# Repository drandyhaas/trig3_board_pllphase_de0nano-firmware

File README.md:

# trig3_board_pllphase_de0nano-firmware
Firmware for the Gershow FPGA worm analysis

Open coincidence.qpf with Quartus (tested with version 18.0.0)

## Serial command set
- 0: send the firmware version				
- 1 + byte: set deadticks
- 2 + byte: set firingticks
- 3: toggle output enable
- 4: toggle clk inputs
- 5 + byte: set clock phase (phase shift = byte/128 * 360)
- 6 + byte: set output1 phase mask		
- 7 + byte: set output2 phase mask
- 8: toggle PMT passthrough
- 9: toggle phase step direction
- 10: send histogram (4 bins for now) 
- 11: toggle vetopmtlast
- 12: adjust clock phase (c1)

## outputs
- A6: out1 : coax_out[2] 
- B6: out2 : coax_out[3] 
- N11: test pulse : coax_out[0]
- P9: 4x clock for test pulse : coax_out[1]
- F9: phase shifted? input clock : coax_out[4] 
- E7: lvds clock (4x) phase shifted : coax_out[5]
- C11: echos differential clock input
- E11: echos single ended clock input
- J13 - active clock
- P11 - clock bad 0
- D8 - clock bad 1

## inputs
- R9/T9 - differential clock input (note that board has resistor networks to accept negative going ac coupled signal)
- A8 - singled ended clock input
- R16/P16 - differential pmt input (board has resistor network to accept AC coupled differential signal)
- L15 - single ended pmt input

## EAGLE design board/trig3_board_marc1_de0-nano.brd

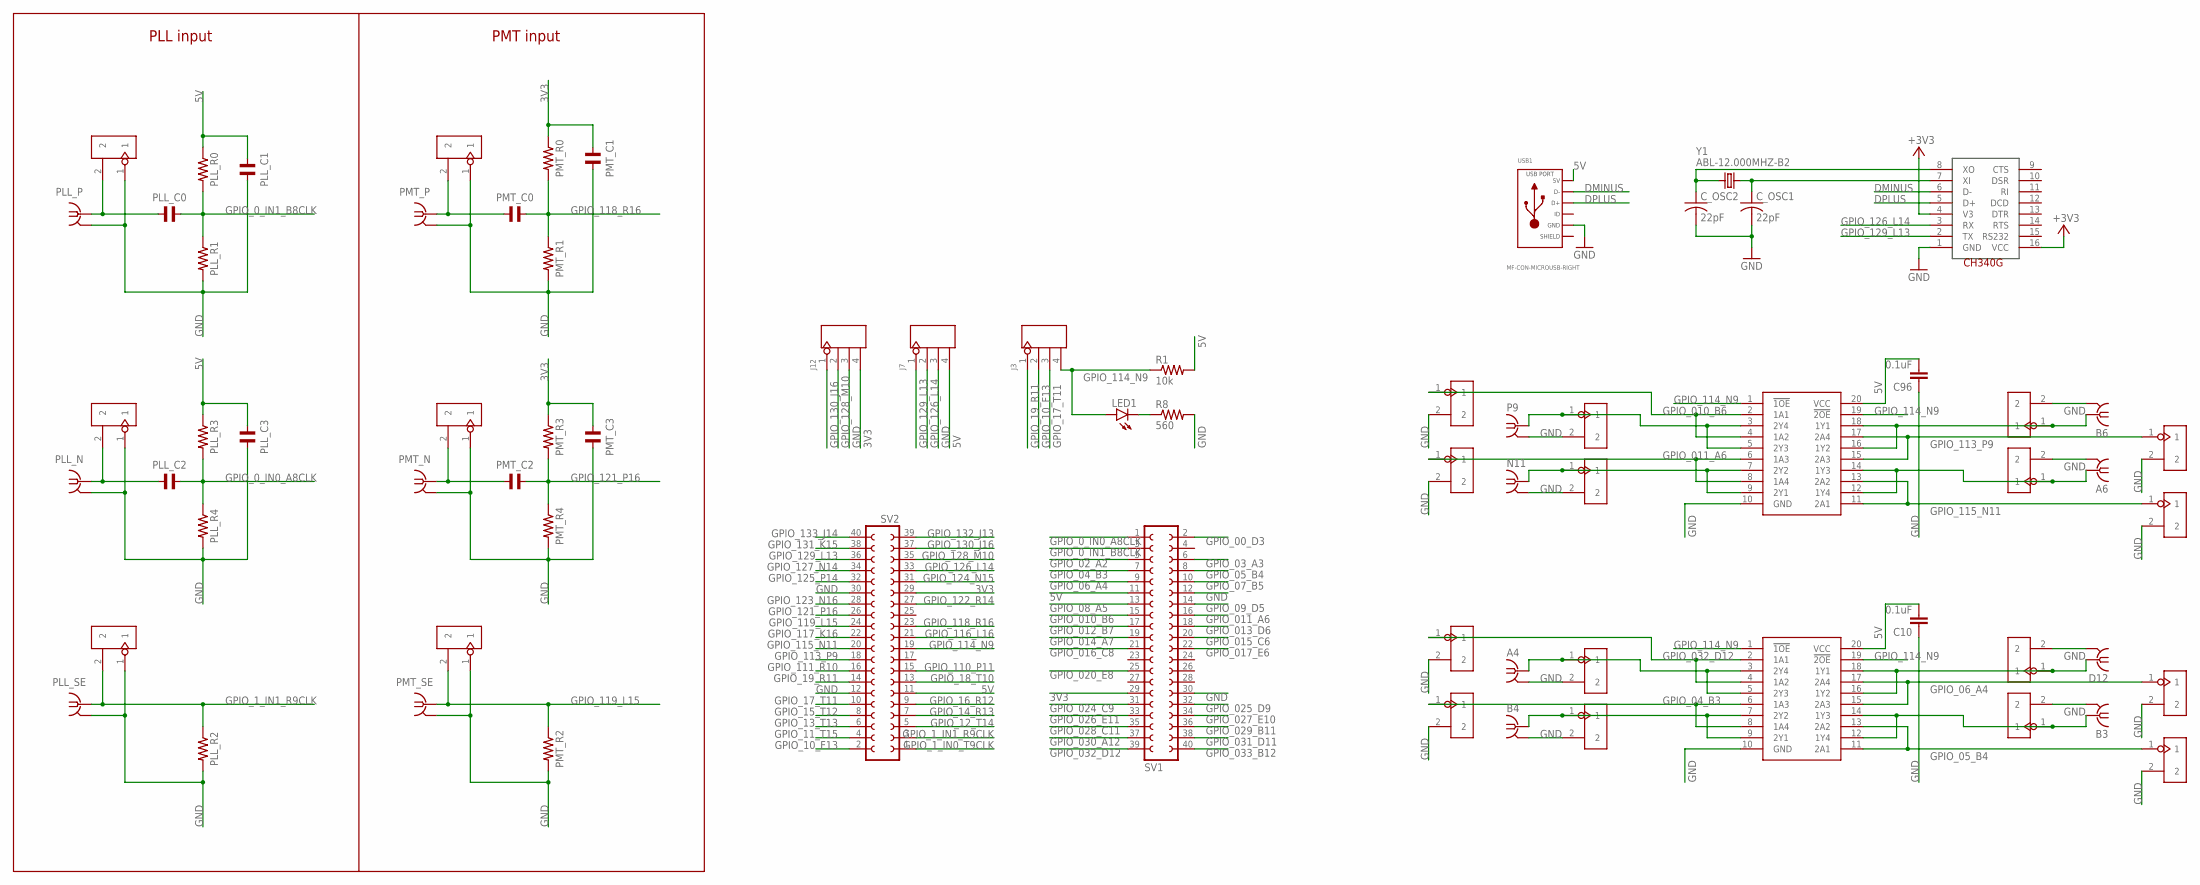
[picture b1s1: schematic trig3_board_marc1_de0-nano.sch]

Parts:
A4, A6: BU-SMB-V
B3, B4, B6: BU-SMB-V
C10, C96: 0.1uF; 0805
C_OSC1, C_OSC2: 22pF; C0603
D12: BU-SMB-V
J3, J7, J12: 4p-2.54; H4-2.54
LED1: red; CHIP-LED0805
N11: BU-SMB-V
OJ41, OJ42, OJ43, OJ44, OJ45, OJ46, OJ47, OJ48, OJ89, OJ90, OJ91, OJ92, OJ93, OJ94, OJ95, OJ96: 2p-2.54; H2-2.54
P9: BU-SMB-V
PLL_C0, PLL_C2: 1uF; C0805
PLL_C1: 0.1uF; C0805
PLL_C3: CAPACITOR_NP_0805; C0805
PLL_N: BU-SMB-V
PLL_N_J, PLL_N_J1: 2p-2.54; H2-2.54
PLL_P: BU-SMB-V
PLL_P_J: 2p-2.54; H2-2.54
PLL_R0, PLL_R1, PLL_R3, PLL_R4: RESISTOR_0805; R0805
PLL_R2: 50ohm; R0805
PLL_SE: BU-SMB-V
PMT_C0, PMT_C2: 1uF; C0805
PMT_C1: 0.1uF; C0805
PMT_C3: CAPACITOR_NP_0805; C0805
PMT_N: BU-SMB-V
PMT_N_J, PMT_N_J1: 2p-2.54; H2-2.54
PMT_P: BU-SMB-V
PMT_P_J: 2p-2.54; H2-2.54
PMT_R0, PMT_R1, PMT_R3, PMT_R4: RESISTOR_0805; R0805
PMT_R2: 50ohm; R0805
PMT_SE: BU-SMB-V
R1: 10k; R0805
R8: 560; R0805
SV1, SV2: FE20-2
U340G: CH340G; SOIC16
USB1: MF-CON-MICROUSB-RIGHT; 10118193-0001LF
VSLUE5, VSLUE11: SN74ACT244DW; SOIC127P1030X265-20N
Y1: ABL-12.000MHZ-B2; HC49US

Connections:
3V3: J12.4, PMT_C1.P$1, PMT_C3.P$1, PMT_R0.P$1, PMT_R3.P$1, SV1.29, SV2.29
5V: C10.2, C96.2, J7.4, PLL_C1.P$1, PLL_C3.P$1, PLL_R0.P$1, PLL_R3.P$1, R1.2, SV1.11, SV2.11, USB1.1 (5V), VSLUE5.20 (VCC), VSLUE11.20 (VCC)
+3V3: U340G.4 (V3), U340G.16 (VCC)
DMINUS: U340G.6 (D-), USB1.2 (D-)
DPLUS: U340G.5 (D+), USB1.3 (D+)
GND: A4.2, A4.3 (2), A4.4 (2), A4.5 (2), A6.2, A6.3 (2), A6.4 (2), A6.5 (2), B3.2, B3.3 (2), B3.4 (2), B3.5 (2), B4.2, B4.3 (2), B4.4 (2), B4.5 (2), B6.2, B6.3 (2), B6.4 (2), B6.5 (2), C10.1, C96.1, C_OSC1.2, C_OSC2.2, D12.2, D12.3 (2), D12.4 (2), D12.5 (2), J7.3, J12.3, N11.2, N11.3 (2), N11.4 (2), N11.5 (2), OJ41.2, OJ42.2, OJ43.2, OJ44.2, OJ45.2, OJ46.2, OJ47.2, OJ48.2, OJ89.2, OJ90.2, OJ91.2, OJ92.2, OJ93.2, OJ94.2, OJ95.2, OJ96.2, P9.2, P9.3 (2), P9.4 (2), P9.5 (2), PLL_C1.P$2, PLL_C3.P$2, PLL_N.2, PLL_N.3 (2), PLL_N.4 (2), PLL_N.5 (2), PLL_N_J.1, PLL_N_J1.1, PLL_P.2, PLL_P.3 (2), PLL_P.4 (2), PLL_P.5 (2), PLL_P_J.1, PLL_R1.P$2, PLL_R2.P$2, PLL_R4.P$2, PLL_SE.2, PLL_SE.3 (2), PLL_SE.4 (2), PLL_SE.5 (2), PMT_C1.P$2, PMT_C3.P$2, PMT_N.2, PMT_N.3 (2), PMT_N.4 (2), PMT_N.5 (2), PMT_N_J.1, PMT_N_J1.1, PMT_P.2, PMT_P.3 (2), PMT_P.4 (2), PMT_P.5 (2), PMT_P_J.1, PMT_R1.P$2, PMT_R2.P$2, PMT_R4.P$2, PMT_SE.2, PMT_SE.3 (2), PMT_SE.4 (2), PMT_SE.5 (2), R8.2, SV1.12, SV1.30, SV2.12, SV2.30, U340G.1 (GND), USB1.5 (GND), VSLUE5.10 (GND), VSLUE11.10 (GND)
GPIO_00_D3: SV1.2
GPIO_0_IN0_A8CLK: PLL_C2.P$2, PLL_R3.P$2, PLL_R4.P$1, SV1.1
GPIO_0_IN1_B8CLK: PLL_C0.P$2, PLL_R0.P$2, PLL_R1.P$1, SV1.3
GPIO_1_IN0_T9CLK: SV2.1
GPIO_1_IN1_R9CLK: PLL_N_J1.2, PLL_R2.P$1, PLL_SE.1, SV2.3
GPIO_02_A2: SV1.5
GPIO_03_A3: SV1.6
GPIO_04_B3: OJ96.1, SV1.7, VSLUE11.6 (1A3), VSLUE11.8 (1A4)
GPIO_05_B4: OJ94.1, SV1.8, VSLUE11.11 (2A1), VSLUE11.13 (2A2)
GPIO_06_A4: OJ93.1, SV1.9, VSLUE11.15 (2A3), VSLUE11.17 (2A4)
GPIO_07_B5: SV1.10
GPIO_08_A5: SV1.13
GPIO_09_D5: SV1.14
GPIO_010_B6: OJ47.1, SV1.15, VSLUE5.2 (1A1), VSLUE5.4 (1A2)
GPIO_10_F13: J3.2, SV2.2
GPIO_011_A6: OJ48.1, SV1.16, VSLUE5.6 (1A3), VSLUE5.8 (1A4)
GPIO_11_T15: SV2.4
GPIO_012_B7: SV1.17
GPIO_12_T14: SV2.5
GPIO_013_D6: SV1.18
GPIO_13_T13: SV2.6
GPIO_014_A7: SV1.19
GPIO_14_R13: SV2.7
GPIO_015_C6: SV1.20
GPIO_15_T12: SV2.8
GPIO_016_C8: SV1.21
GPIO_16_R12: SV2.9
GPIO_017_E6: SV1.22
GPIO_17_T11: J3.3, SV2.10
GPIO_18_T10: SV2.13
GPIO_19_R11: J3.1, SV2.14
GPIO_020_E8: SV1.25
GPIO_024_C9: SV1.31
GPIO_025_D9: SV1.32
GPIO_026_E11: SV1.33
GPIO_027_E10: SV1.34
GPIO_028_C11: SV1.35
GPIO_029_B11: SV1.36
GPIO_030_A12: SV1.37
GPIO_031_D11: SV1.38
GPIO_032_D12: OJ95.1, SV1.39, VSLUE11.2 (1A1), VSLUE11.4 (1A2)
GPIO_033_B12: SV1.40
GPIO_110_P11: SV2.15
GPIO_111_R10: SV2.16
GPIO_113_P9: OJ45.1, SV2.18, VSLUE5.15 (2A3), VSLUE5.17 (2A4)
GPIO_114_N9: J3.4, LED1.A, R1.1, SV2.19, VSLUE5.1 (!1OE), VSLUE5.19 (!2OE), VSLUE11.1 (!1OE), VSLUE11.19 (!2OE)
GPIO_115_N11: OJ46.1, SV2.20, VSLUE5.11 (2A1), VSLUE5.13 (2A2)
GPIO_116_L16: SV2.21
GPIO_117_K16: SV2.22
GPIO_118_R16: PMT_C0.P$2, PMT_R0.P$2, PMT_R1.P$1, SV2.23
GPIO_119_L15: PMT_N_J1.2, PMT_R2.P$1, PMT_SE.1, SV2.24
GPIO_121_P16: PMT_C2.P$2, PMT_R3.P$2, PMT_R4.P$1, SV2.26
GPIO_122_R14: SV2.27
GPIO_123_N16: SV2.28
GPIO_124_N15: SV2.31
GPIO_125_P14: SV2.32
GPIO_126_L14: J7.2, SV2.33, U340G.3 (RX)
GPIO_127_N14: SV2.34
GPIO_128_M10: J12.2, SV2.35
GPIO_129_L13: J7.1, SV2.36, U340G.2 (TX)
GPIO_130_J16: J12.1, SV2.37
GPIO_131_K15: SV2.38
GPIO_132_J13: SV2.39
GPIO_133_J14: SV2.40
unnamed: PMT_C0.P$1, PMT_P.1, PMT_P_J.2
unnamed: PMT_C2.P$1, PMT_N.1, PMT_N_J.2
unnamed: LED1.C, R8.1
unnamed: PLL_C0.P$1, PLL_P.1, PLL_P_J.2
unnamed: PLL_C2.P$1, PLL_N.1, PLL_N_J.2
unnamed: C_OSC1.1, U340G.7 (XI), Y1.1
unnamed: C_OSC2.1, U340G.8 (XO), Y1.2
OUT21: B6.1, OJ44.1, VSLUE5.16 (1Y2), VSLUE5.18 (1Y1)
OUT22: A6.1, OJ43.1, VSLUE5.12 (1Y4), VSLUE5.14 (1Y3)
OUT23: OJ41.1, P9.1, VSLUE5.3 (2Y4), VSLUE5.5 (2Y3)
OUT24: N11.1, OJ42.1, VSLUE5.7 (2Y2), VSLUE5.9 (2Y1)
OUT45: D12.1, OJ92.1, VSLUE11.16 (1Y2), VSLUE11.18 (1Y1)
OUT46: B3.1, OJ91.1, VSLUE11.12 (1Y4), VSLUE11.14 (1Y3)
OUT47: A4.1, OJ89.1, VSLUE11.3 (2Y4), VSLUE11.5 (2Y3)
OUT48: B4.1, OJ90.1, VSLUE11.7 (2Y2), VSLUE11.9 (2Y1)
SLD: USB1.S1 (SLD), USB1.S2 (SLD), USB1.S3 (SLD), USB1.S4 (SLD)

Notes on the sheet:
PLL input
PMT input

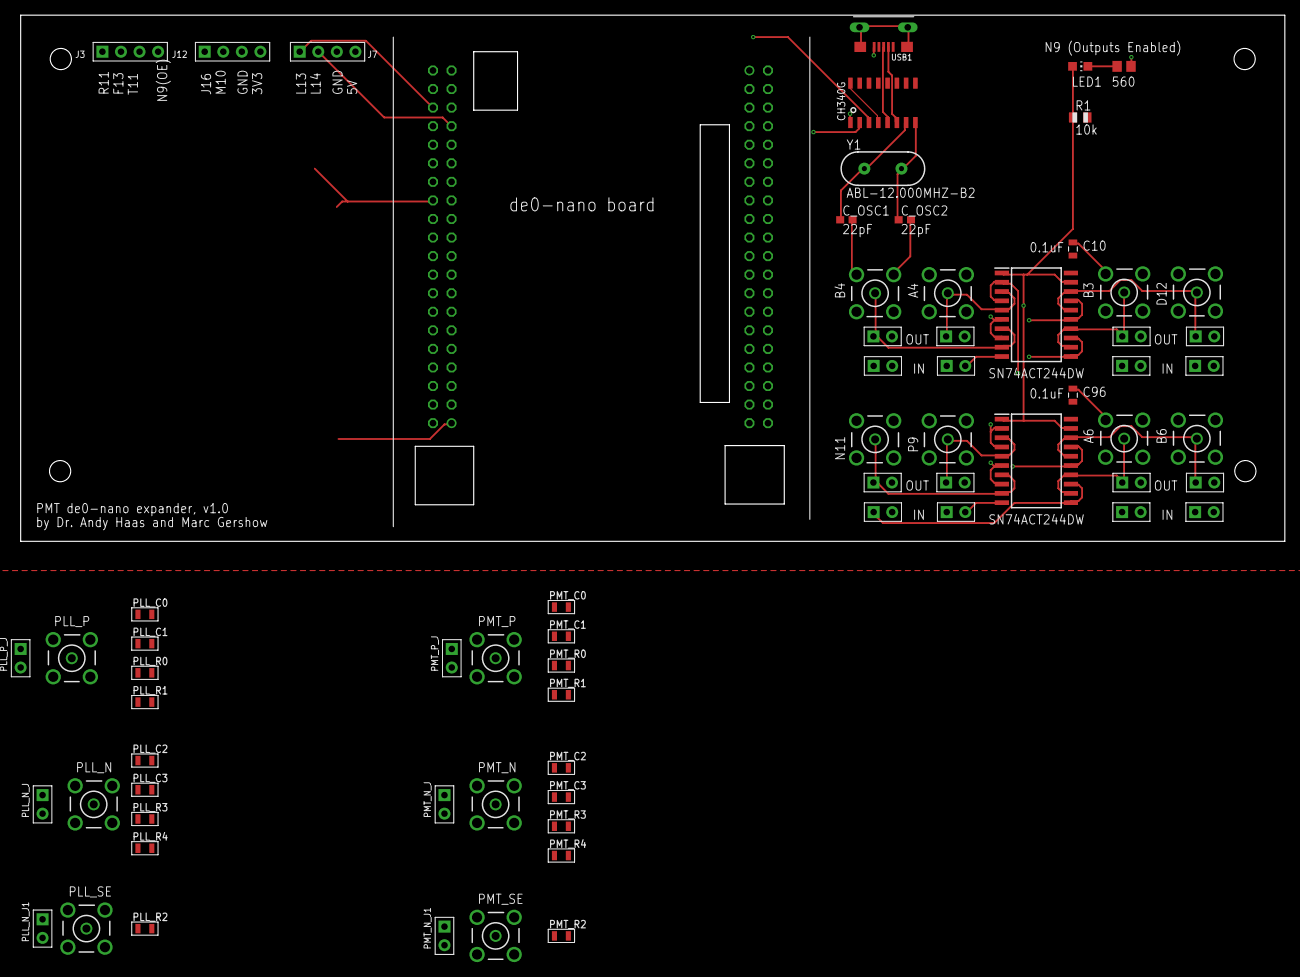
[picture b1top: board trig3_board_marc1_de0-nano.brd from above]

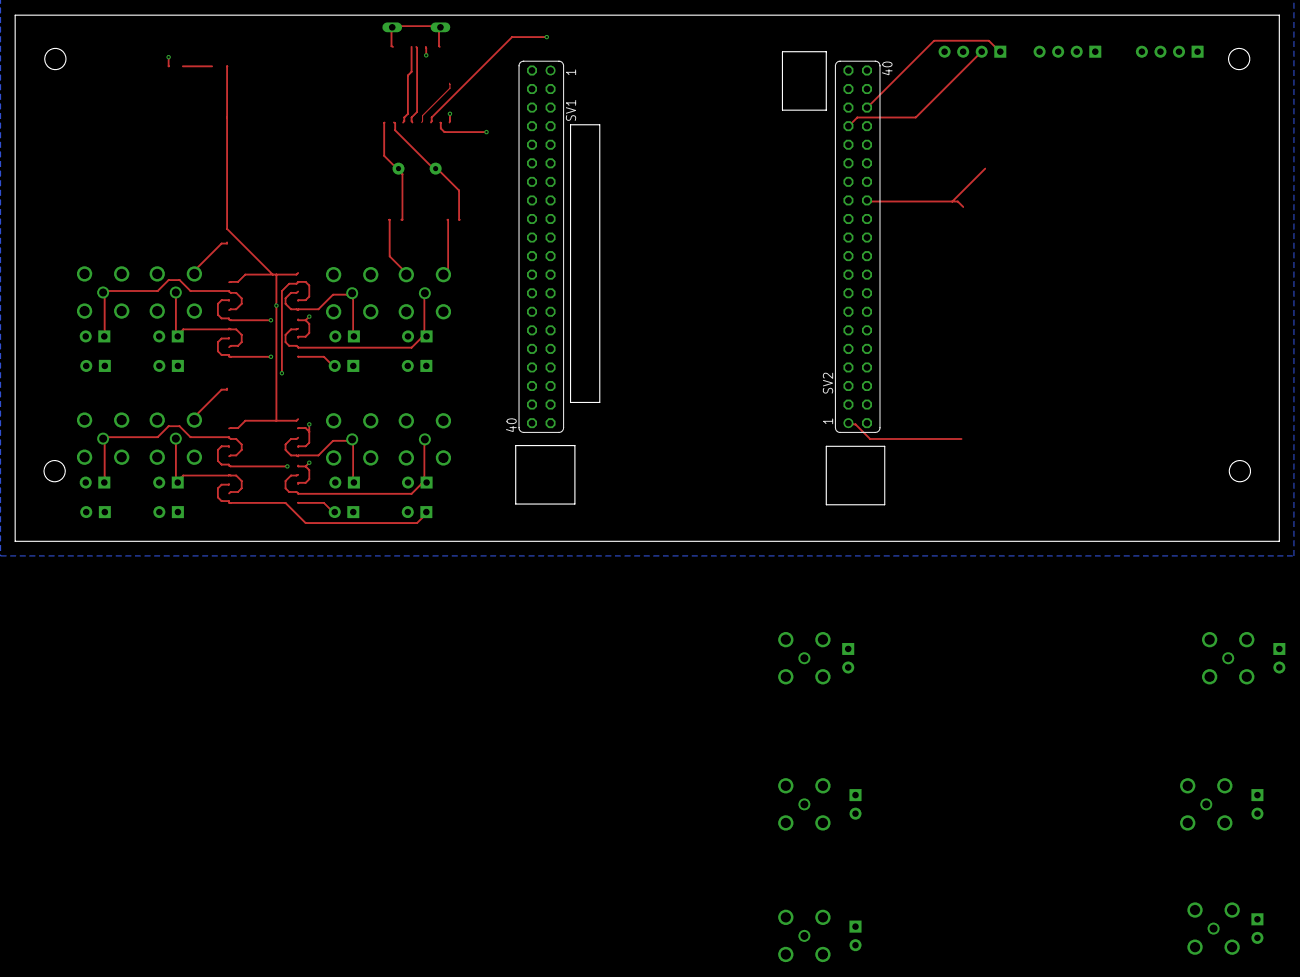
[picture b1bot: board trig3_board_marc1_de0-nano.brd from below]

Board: 4 copper layers, 173.0 x 72.0 mm, 71 parts (2 on the bottom side), 44 nets.

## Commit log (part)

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2020-01-23 initial checkin, working with 4 bins
2020-01-23 cleaner
2020-01-23 after compilation
2020-01-23 cleaner 2
2020-01-23 update for new location
2020-01-23 update to 8 bins
2020-02-19 changed 80Mhz clock input to LVDS
    required changes to logic family on some pins 3.3V -> 2.5V
    required override IO_MAXIMUM_TOGGLE_RATE to 0 MHz on enable outputs
2020-02-19 wrote programming file
2020-02-19 added single ended clock input at A8 with automatic selector
2020-02-20 changed pll bandwidth to low
    added debugging output signals to PLL
2020-02-25 added ability to reset PLL phase
    switched default clock to 70 MHz
2020-02-25 programs ok on lab computer
2020-02-25 board
2020-02-25 slim it down and add usb-serial
2020-02-25 for slimmed down board
2020-02-25 now set phase directly instead of incrementally
    to adjust phase: 5 byte; phase is set to byte by resetting PLL and then stepping byte times.
2020-02-25 set photon detection by mask
2020-02-26 histogram outputs 8 bins
2020-03-12 updated board schematics: input circuit redesign
2020-09-24 trying to generate ipi histogram; veto pulses too close together
2020-09-24 added serial command to set veto counter; updated firmware version
2020-09-24 get version works
2020-09-25 changed pin assignments
2020-09-29 updated to give debugging outputs
    cycle toggle on c16
    any photon on e7
2020-09-30 added debug - put clock input into lvds
2020-10-05 trimming down led_4.v and rewriting to use shift registers, eliminate for loops
2020-10-05 trying to fix compile warnings in master (thought i was on other branch)
    sure are a lot of them!
2020-10-05 ready to try
    should not change function, just cleaned up code
2020-10-06 clock keeps switching to 50 khz
    very weird
2020-10-06 more debugging outputs
2020-10-07 messed with PLL settings
2020-10-07 changed the way phase shifting works
    now shift the 70 mhz clock and feed shifted 70 to 3rd pll for the 4/1 split
2020-10-08 using latches for lvds input helps a lot
2020-10-08 registering input photons to ddr clock, phase shifted a little
    hope this works!
2020-10-08 now pll is wonky again
    ugh
2020-10-08 at this point, PLL locks
    nothing works, but pll locks
2020-10-08 compared to last commit before branching, does not lock pll now
2020-10-13 locks, but slowly
2020-10-13 building up pll blocks
    created pll bsf and enabled dynamic phase shifting - will it lock?
2020-10-13 connected serial control to set phase
2020-10-13 hard coded phase counter select
    now correctly shifts clock without shifting test pulse
2020-10-14 attempted to restore functionality
    will it lock? will it work?
2020-10-15 removed binning and masking element
2020-10-15 removed lvds_rx block
2020-10-15 removed almost everything from before
    wtf
2020-10-15 removed pmt input and switched clock echo to p15
    locks
2020-10-15 changed clock echo to c11
    does not lock
2020-10-15 inserted iobuf between clk and c11
    does not lock
2020-10-15 connected to p15 via iobuf
    locks
2020-10-15 disconnected p15 output
    locks
2020-10-15 changed disconnected output to c11
    still locks
2020-10-15 connected clock echo to c11 via iobuf with output enable
    locks when output disabled
2020-10-15 connected to j13
    does not lock if output enabled
2020-10-15 connected to f9
    sometimes locks when toggle output enable (oddly line driver does not respond)
2020-10-15 elminated clock echo output
    performance is improved
2020-10-16 set pll4lvds to no compensation
2020-10-16 added lvds_reset output to check that condition
2020-10-16 OR of lvds output for testing
    do not see any signal
2020-10-16 removed lvds reset; shift reg output for testing
    now lvds "works" but binning sometimes works and sometimes is random
2020-10-16 rewrote pulse registration
2020-10-16 trying to look at lvds clock on output
2020-10-16 got rid of lvds
    just doing dff and pulse generator
2020-10-17 modified pulse detection to be more robust; added finer control to which bins count
    added more debugging outputs
    version 21
2020-10-17 set bandwidth to high, enabled auto reset
    locking is worse
2020-10-17 added output enable control to extra clocks
    helps some; drops lock for a few ms every few hundred ms
2020-10-17 set all outputs to 2.5 V standard
    now locks without dropping when supplemental outputs are off
2020-10-17 set slew rates to 0
    appears to work, but very flaky with phase; clearly cross-talk is a huge problem
2020-10-17 disabled extra clock outputs
2020-10-17 disconnected all non-essential outputs
    seems stable, except when phase puts transition near edge
2020-10-17 reconnected p9 output
    but any photon doesn't show
2020-10-23 restored outputs
    we are now providing a more stable input clock, which fixes all problems
2020-10-23 added 8 bin demultiplexer and histogram creation
    lets see if it works!
2020-10-23 all of our problems are not solved
2020-10-27 was registering in wrong bins
    now doesn't work at all
2020-10-27 a couple of simple debug tests
    tied 4x clock to vcc/gnd; register photon to 2x clock
2020-10-28 rewrote to make synchronous
    different debugging outputs
2020-10-29 changed decimation & output debug; phase shifted valid clocks by 45
2020-10-29 added synchronous design elements
    will it help? adds latency, that's for sure
2020-10-29 generate test pulse directly from pll
    with lvds input decimated, test pulse height on scope changed with phase shift (even though nothing in the test pulse path should have been sensitive to phase shift)
    now generating test pulse from pll directly
2020-10-29 now trying decimation of test pulses
    previously sent a 4 ns test pulse every 10 cycles from PLL - worked great
    now generate a 4 ns pulse every cycle and use and gate decimation to knock down to 1/10 rate
2020-10-29 shortened test pulse width to 1.82 ns
    decimation worked fine.
    no other changes, just test pulse duty cyle
2020-10-29 works fine with 1.8ns pulse and decimation
    output pulse height is now phase sensitive though, so that's just a short pulse effect
2020-10-29 connected lvds test pulse input instead
    now it doesn't work - binning is all messed up
2020-10-29 register input pulse to 1250 MHz clock generated from 70 MHz clock
    looks like butt;
    repeatable butt
2020-10-29 connected test pulse to 1250 MHz register
    works fine
2020-10-29 added logic to allow you to pick between test pulse and lvds input
    test pulse works great; lvds input is butt
2020-10-29 output pulses registered to laser clock (not phase shifted laser clock)
    pll test pulse works great
    lvds input does not
2020-10-29 added requirement that input be high for 2 cycles (0.8-1.6 ns, depending on when signal arrives))
2020-10-29 debounce2to2 helps with but does not fix real input
    completely clobbers pll fake
2020-10-29 switched to edge detector I found online
2020-10-29 resetting to 9df30fd, I hope
2020-10-29 more debugging outputs
    changed to and gates on input and using and-gate output to set output pulses with edge detector
    as expected, increases amount of crossover on pll test pulse input
    ch1 works fine on lvds input, but ch2 is messed up
2020-10-29 changed phase of plls from 45/225 to 180/0
    chnages the phase offset for the problem graph, but out0 still has issues
2020-10-29 fixed problem! disconnected in-phase clock output (for valid1)
    was on pin j13 which is near k15,k16 input pair for lvds
2020-10-29 changed back to edge triggered register
    looks great!
2020-10-29 changed duty cycle to 43%
    this eliminates the double counts, but leaves some dead-zone. This might be desireable - allows for pmt signal jitter - but if not, could add second, slightly phase shifted signals and or them
    could not set duty cycle to 48%, my desired setting
2020-10-29 cleaned up interface, removed unused outputs
    can select internal test or external test now
    oddly, double counting for ~1ns at crossover is back
2020-10-29 set duty cycle to 36% and it's nearly perfect
    with external test pulse input decimated
2020-11-03 added sweeping histogram
    changes number of bytes sent to computer via serial and format of histogram
    moved output clock to p9
    version to 23
2020-11-06 histogram doesnt work but otherwise ok
    need to disable all non-essential outputs to reduce crosstalk
2020-12-01 disabled debugging outputs
2020-12-01 cosmetic changes
2020-12-01 tried to address some warnings
    removed the histogram generator
    rewrote pll_sweeper using blocking commands
2020-12-01 plls and photons pulses clock on phase shifted
    changed latch clock to be phase shifted clock
2020-12-01 reconnected 2 element histogram
2020-12-01 simplified and played with pll settings
    think we need to rethink synchronization
2020-12-01 messed with synchronizers on edge detector
2020-12-01 register pulse in two steps
2020-12-01 double register to same clock
    just because it wasn't working - turns out laser was off
2020-12-02 Revert "double register to same clock"
    This reverts commit 526a030d178c006efa81a428a3fdff88c8da50ac.
2020-12-02 lots of changes; no timing violations now
    using fifos to cross clock domains
    rewrote edge detector to use toggle flip flop and synchronous design
    let's hope!
2020-12-02 generated programming file
2020-12-02 bypassed fifos
    wasn't working with fifos, let's see if they are the problems
2020-12-02 reset pll1 to 180 degrees out of phase & rewrote edge detector in verilog
2020-12-02 changed to phae shift clock registration
    one channel slightly more counts than other with noise input; double counts at transition
2020-12-02 set duty cycle to 43% and shifted ps_clock by -25 degrees
    random noise; ch1 has 5% (400/8k) less counts than ch0
    driven looks the same (6.65M _+/- .01M)
2020-12-02 connected test to external input
2020-12-03 added veto last pmt cycle option
    also changed back to using laser clock rather than phase shifted clock
2020-12-03 changed decimator
    no effect on pulse offset issue
2020-12-03 changed to phase shifted clock for alignment
    becomes more symmetric on the test input (but not exactly)
    equal ch1 and ch0 (4k) on white noise with veto off
    ch1 drops to 3k, ch0 to 2k when veto is on
2020-12-03 changed to 180 degree out of phase shifted clock
    with vetopmtlast off, 4500 for ch1 and 4k for ch0
    with vetoomtlast on, 2.75k for ch1 and 3.5k for ch0
    so weird
2020-12-03 use start and not stop clocks to set valid region
    first step towards setting valid width dynamically
2020-12-03 changed phase step to 5 degrees
    incremented version to 26
2020-12-03 veto now goes 3 deep
2020-12-03 register pulse in two steps, first to phase shifted clock, then to not shifted clock
2020-12-03 works!
    made a meaningless change so I could have a commit;
    looks like about 20/150k cross talk (<15%)
2020-12-03 progress towards setting phase steps individually
    function should not have changed, but architecture is in place if this runs correctly
2020-12-04 changed serial interface and added labview controls to this repository
2020-12-04 connected leds to command in serial processor
    does not work right now, debugging
2020-12-04 doesn't work
2020-12-07 changes to serial processor
    attempting to fix bugs and get more detailed debug output in lights
2020-12-08 Update pmt demultiplexer control.vi
    histogram does not work;
    bins trim from the front, not back, which is weird
2020-12-08 added (unneeded) histogram debugging
    fixed issues in labview
2020-12-09 added 10 bin histogram using 2 plls
    inefficient, but it works
2020-12-10 seems to work
    internal test input does not work with histogram
    both test inputs interact badly with cycles to veto (number of detected events goes up when veto is turned on)
2020-12-10 added lock output for error signalling
    also added ability (not tested) to output detections as level changes rather than pulses
2020-12-11 working on lv code
    needs rework on histogram
2021-01-19 encode photons as level change button added
    not sure what's going wrong with histogram
2021-01-19 fixed bug that was doubling pulse length
    coding as level switches now works but doesn't need to

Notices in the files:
parts and their libraries:
SparkFun-Capacitors: Licensing: Creative Commons ShareAlike 4.0 International - https://creativecommons.org/licenses/by-sa/4.0
